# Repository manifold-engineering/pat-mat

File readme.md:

# Pat-Mat
**Phantom And Tonader - Microphone Adapter Thing**

World of professional audio has moved to phantom power for condenser microphones decades ago. But there are good microphones from older days out that used other standards - most notably tonader power (also called T12, T-Power or AB power). Pat-Mat (Phantom And Tonader - Microphone Adapter Thing) is a professional-grade adapter designed to convert standard 48V phantom power into 12V tonader power.

Pat-Mat consists of single PCB designed to fit inside standard XLR male connector (output connctor, like Neutrik NC3MXX series), allows for fit for standard cable relief. Users may choose cable and microphone connector for their specific microphones (DIN, Tuchel...).

## Hardware design

Hardware design is meant be as simple as possible.

12V is prepared by voltage divider resistors (R3, R4) to Zener diode. Audio signal is by connected through C1 and C3 capacitors.

All schematics and PCB design files are available in the `/pat-mat-pcb` directory in KiCAD 8 format. There is output folder with gerber file outputs for manufacturing. They were successfully manufactured by JLC-PCB. Simple BOM file with links to TME is provided. Since Pat-Mat design is simple and only need standard components, it should be possible to source parts from your favourite supplier.

**In order to fit to standard XLR connector, order you PCB 1.2 mm thick. 1.6 mm wont fit!**

## Assembly

*(note: This is development version, + and G pins are flipped. It is fixed in published version.)*

First populate SMD components onto PCB (or preferably order assmebled PCBs)

Then solder PCB into XLR pins

Then add cable of your choice. You mich have to trim some strands of shielding to fit into PCB. You might have to let shorter loose wires than you would do whe soldering standard connector.

Add cable relief

And finish cable like you would the standard way. 

## License

This project is open-source under the MIT License—feel free to use, modify, and improve Pat-Mat for your own audio needs.

---

**"A Je To!"**

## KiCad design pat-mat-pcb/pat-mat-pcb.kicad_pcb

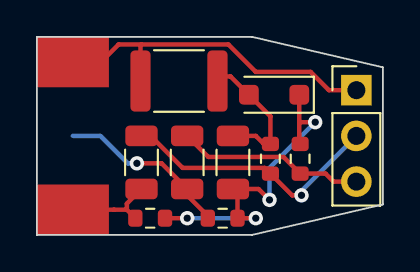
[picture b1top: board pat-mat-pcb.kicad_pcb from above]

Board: 2 copper layers, 19.2 x 11.0 mm, 11 parts (0 on the bottom side), 7 nets.

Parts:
C1, C2, C3: C; C_1206_3216Metric
C4: XLR_PCB
D1: 12V_Zener; D_SOD-123F
J1: Conn_01x03_Pin; PinHeader_1x03_P2.54mm_Vertical
L1: 1mH; L_1812_4532Metric
R1, R2: 180R; R_0603_1608Metric
R3, R4: 680R; R_0603_1608Metric

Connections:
unnamed: C3.2, C4.3 (Cold), R4.1
unnamed: C4.1 (GND), J1.1, L1.2
unnamed: C1.2, C4.2 (Hot), R3.1
unnamed: C2.2, D1.2 (A), L1.1, R1.2
unnamed: C2.1, D1.1 (K), R2.2, R3.2, R4.2
unnamed: C1.1, J1.2, R1.1
unnamed: C3.1, J1.3, R2.1

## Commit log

2024-10-19 readme fix
